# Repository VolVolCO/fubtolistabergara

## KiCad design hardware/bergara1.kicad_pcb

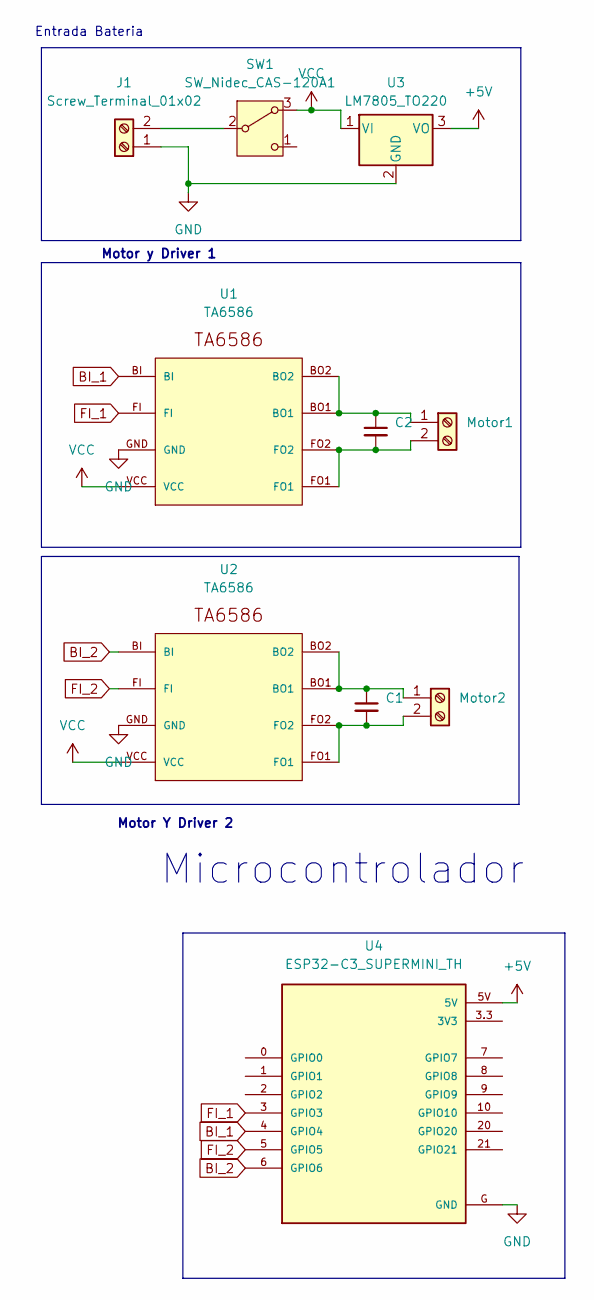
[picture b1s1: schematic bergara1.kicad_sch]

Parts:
C1, C2: C_Small; C_Disc_D4.3mm_W1.9mm_P5.00mm
J1: Screw_Terminal_01x02; TerminalBlock_bornier-2_P5.08mm
Motor1, Motor2: Screw_Terminal_01x02; TerminalBlock_bornier-2_P5.08mm
SW1: SW_Nidec_CAS-120A1; TerminalBlock_Xinya_XY308-2.54-3P_1x03_P2.54mm_Horizontal
U1, U2: TA6586; TA6586-FOOTPRINT
U3: LM7805_TO220; TO-220-3_Vertical
U4: ESP32-C3_SUPERMINI_TH; MODULE_ESP32-C3_SUPERMINI

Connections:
+5V: U3.3 (VO), U4.5V
BI_1: U1.BI, U4.4 (GPIO4)
BI_2: U2.BI, U4.6 (GPIO6)
FI_1: U1.FI, U4.3 (GPIO3)
FI_2: U2.FI, U4.5 (GPIO5)
GND: J1.1, U1.GND, U2.GND, U3.2 (GND), U4.G (GND)
unnamed: J1.2, SW1.2 (B)
unnamed: C2.1, Motor1.1, U1.BO1, U1.BO2
unnamed: C2.2, Motor1.2, U1.FO1, U1.FO2
unnamed: C1.1, Motor2.1, U2.BO1, U2.BO2
unnamed: C1.2, Motor2.2, U2.FO1, U2.FO2
VCC: SW1.3 (A), U1.VCC, U2.VCC, U3.1 (VI)

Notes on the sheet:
Motor Y Driver 2
Motor y Driver 1
Microcontrolador
Entrada Bateria

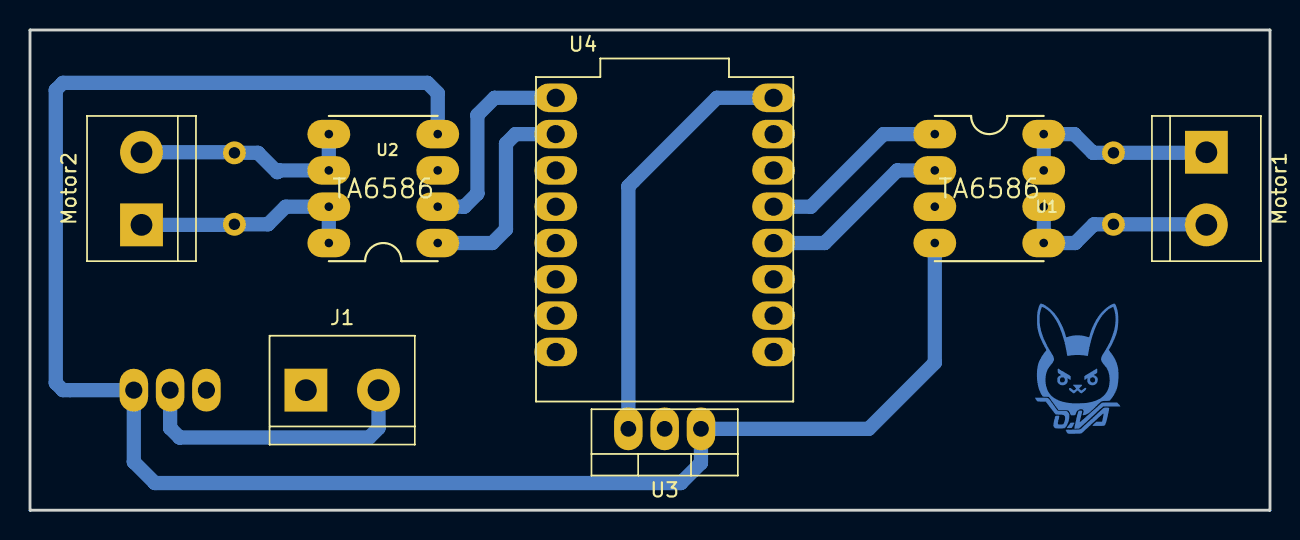
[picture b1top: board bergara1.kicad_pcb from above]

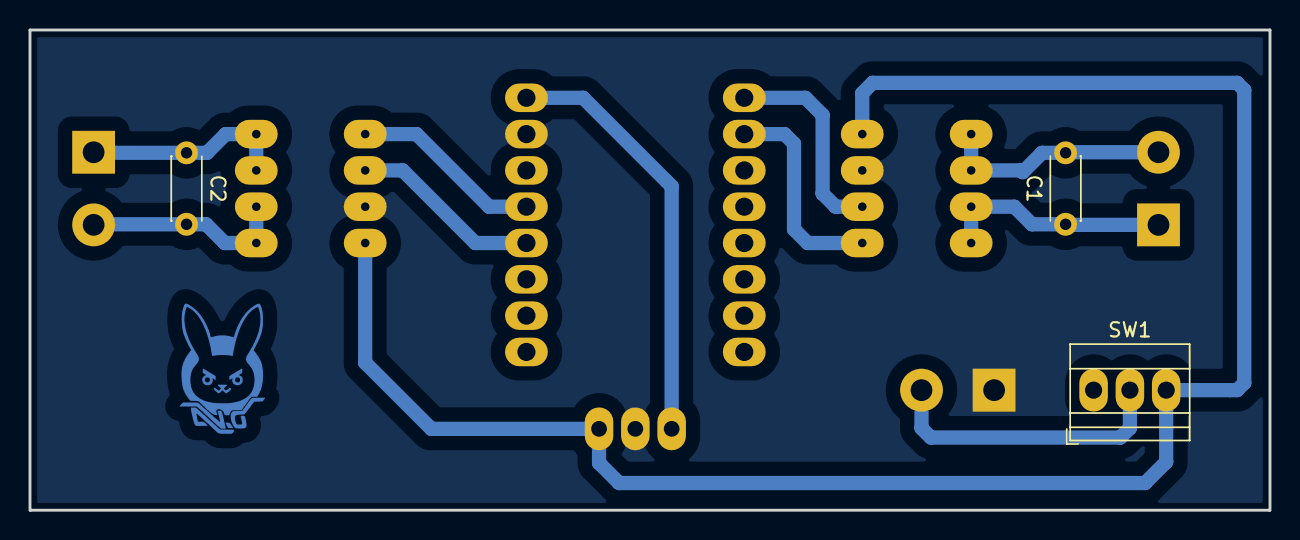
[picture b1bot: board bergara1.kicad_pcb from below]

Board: 2 copper layers, 86.7 x 33.6 mm, 10 parts (3 on the bottom side), 12 nets.

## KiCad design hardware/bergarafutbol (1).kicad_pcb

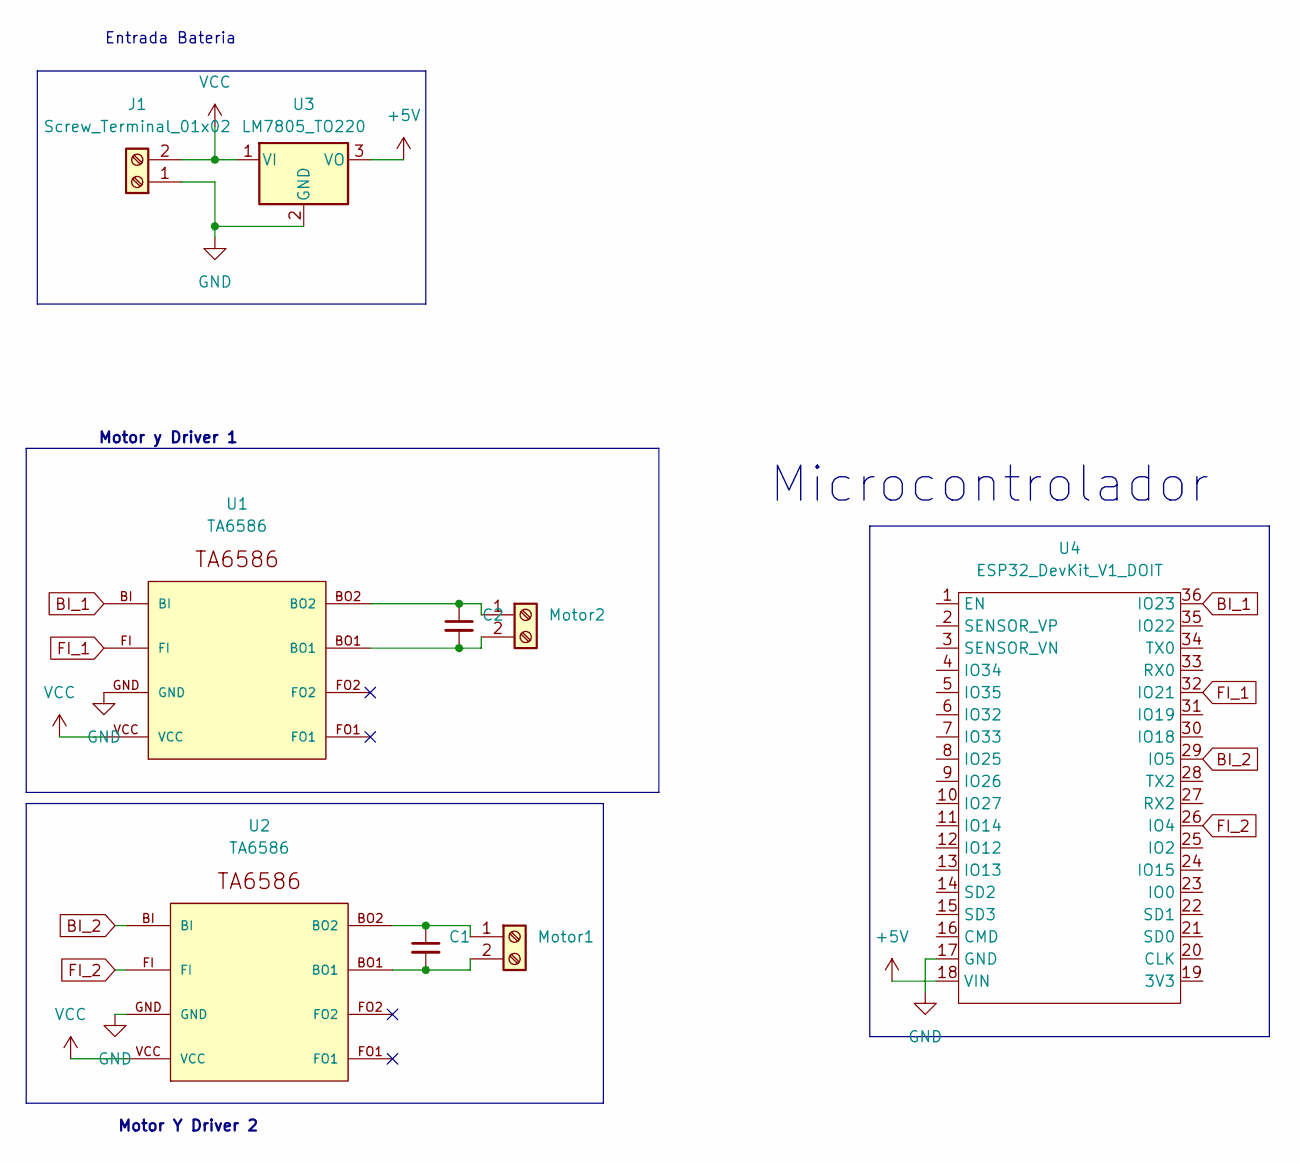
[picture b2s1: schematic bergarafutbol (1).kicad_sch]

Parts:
C1, C2: C_Small; C_0805
J1: Screw_Terminal_01x02; TerminalBlock_bornier-2_P5.08mm
Motor1, Motor2: Screw_Terminal_01x02; TerminalBlock_bornier-2_P5.08mm
U1, U2: TA6586; TA6586-FOOTPRINT
U3: LM7805_TO220; TO-220-3_Vertical
U4: ESP32_DevKit_V1_DOIT; ESP32_DEVKIT_V1_DOIT

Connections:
+5V: U3.3 (VO), U4.18 (VIN)
BI_1: U1.BI, U4.36 (IO23)
BI_2: U2.BI, U4.29 (IO5)
FI_1: U1.FI, U4.32 (IO21)
FI_2: U2.FI, U4.26 (IO4)
GND: J1.1, U1.GND, U2.GND, U3.2 (GND), U4.17 (GND)
unnamed: C1.1, Motor1.1, U2.BO2
unnamed: C1.2, Motor1.2, U2.BO1
unnamed: C2.1, Motor2.1, U1.BO2
unnamed: C2.2, Motor2.2, U1.BO1
VCC: J1.2, U1.VCC, U2.VCC, U3.1 (VI)

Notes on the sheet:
Motor Y Driver 2
Motor y Driver 1
Entrada Bateria
Microcontrolador

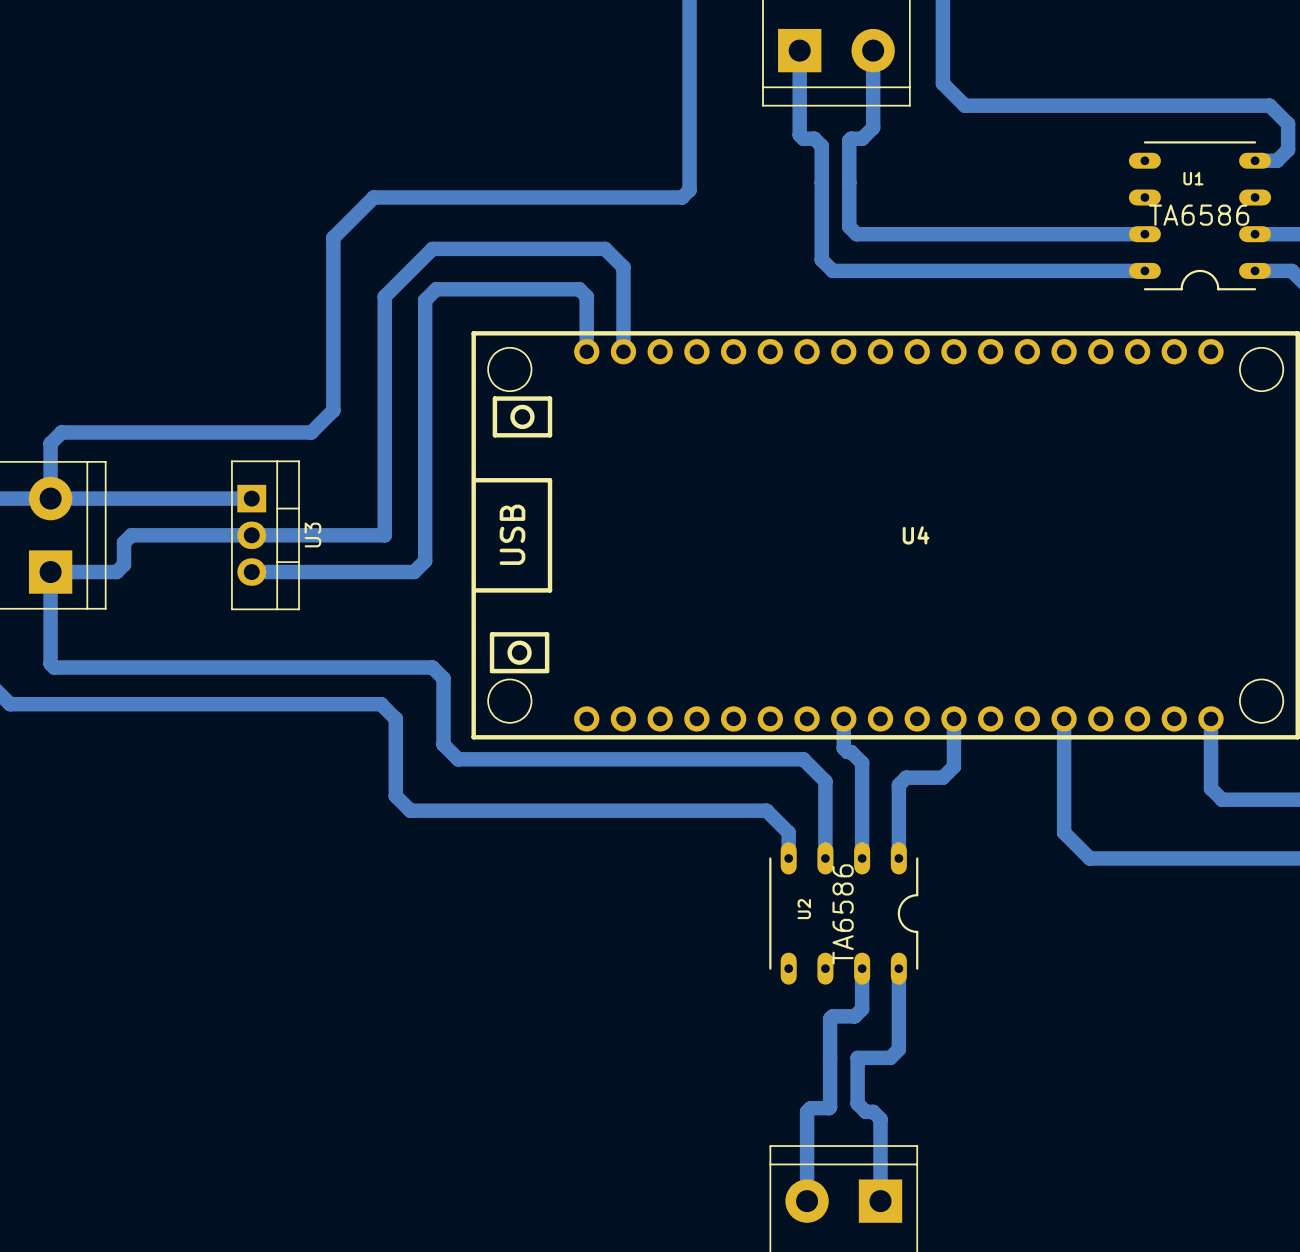
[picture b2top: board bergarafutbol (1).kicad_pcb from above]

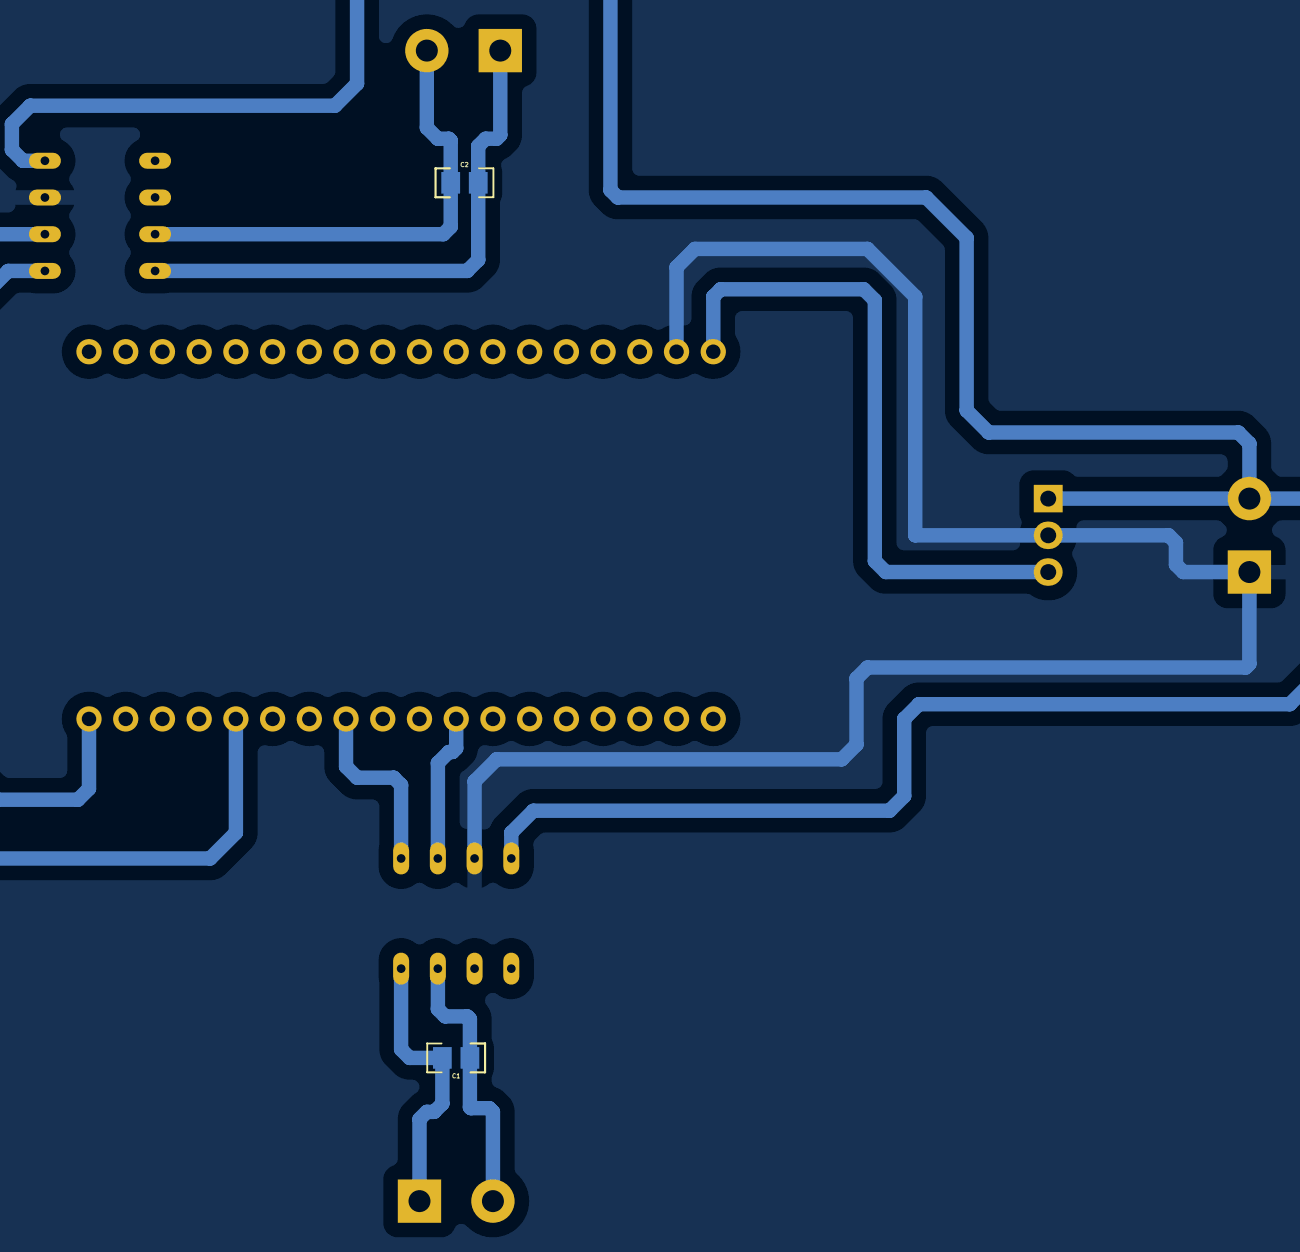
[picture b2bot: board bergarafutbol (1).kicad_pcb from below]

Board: 2 copper layers, 9 parts (2 on the bottom side), 11 nets.

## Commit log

2025-04-15 futbolista commit
2025-05-05 Create hardware
2025-05-13 v13.5
2025-05-13 carpetas adicionales
2025-05-27 Final Futbolista Bergara
2025-05-28 Ultima actualizacion
2025-06-02 PCB y Esquematico Terminado y corregido
2025-06-04 V4.6.25
2025-06-04 Hola
2025-06-24 Codigo Futbol v1, 24/6
